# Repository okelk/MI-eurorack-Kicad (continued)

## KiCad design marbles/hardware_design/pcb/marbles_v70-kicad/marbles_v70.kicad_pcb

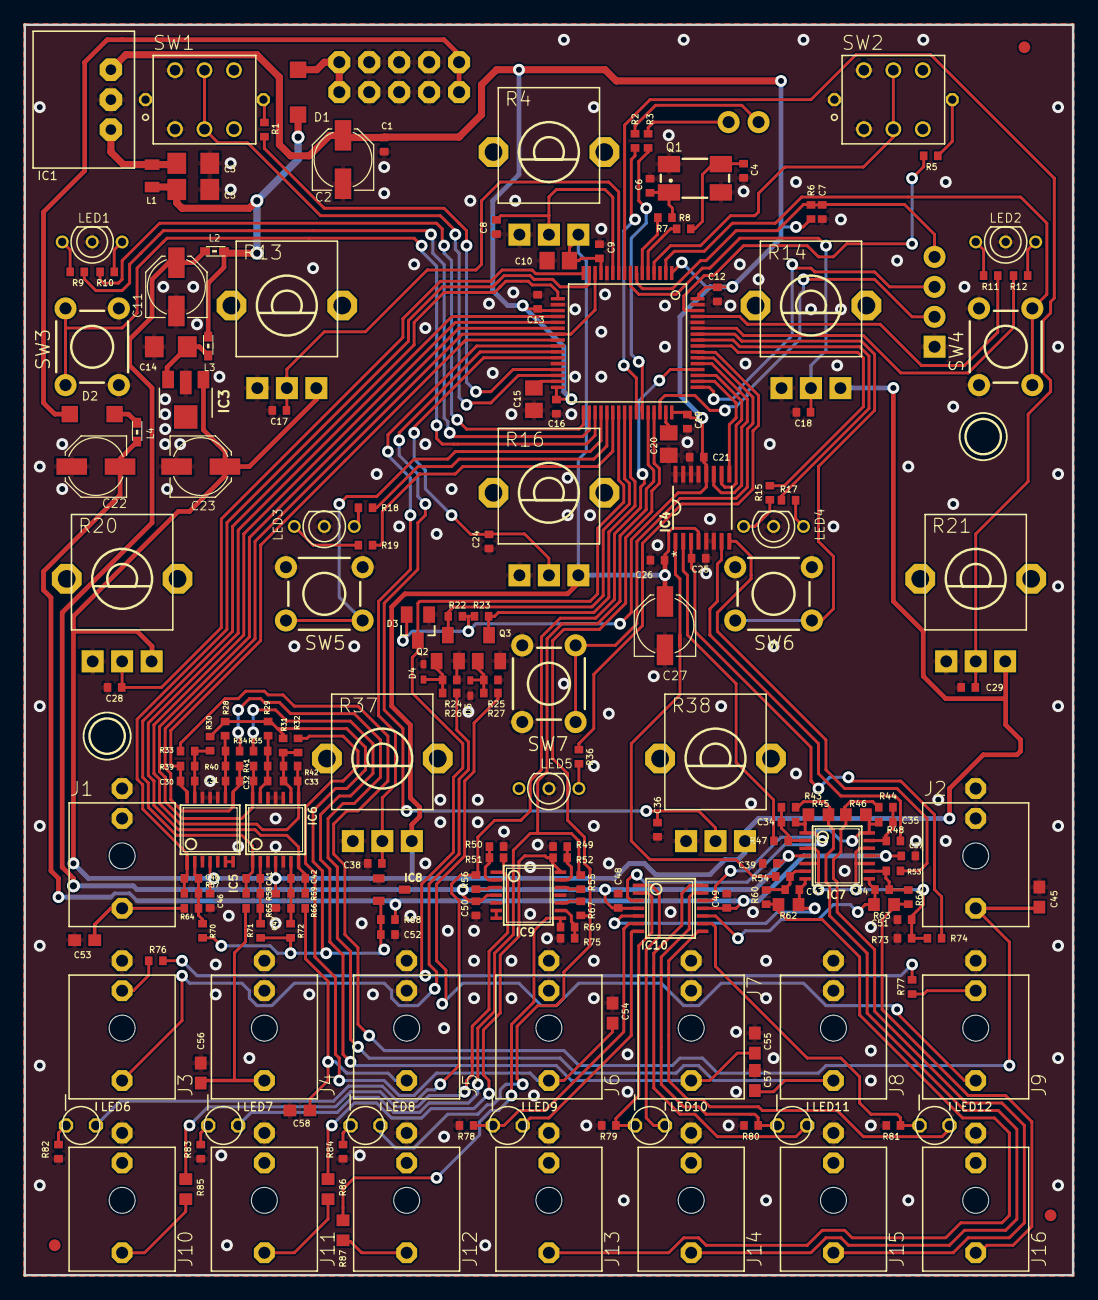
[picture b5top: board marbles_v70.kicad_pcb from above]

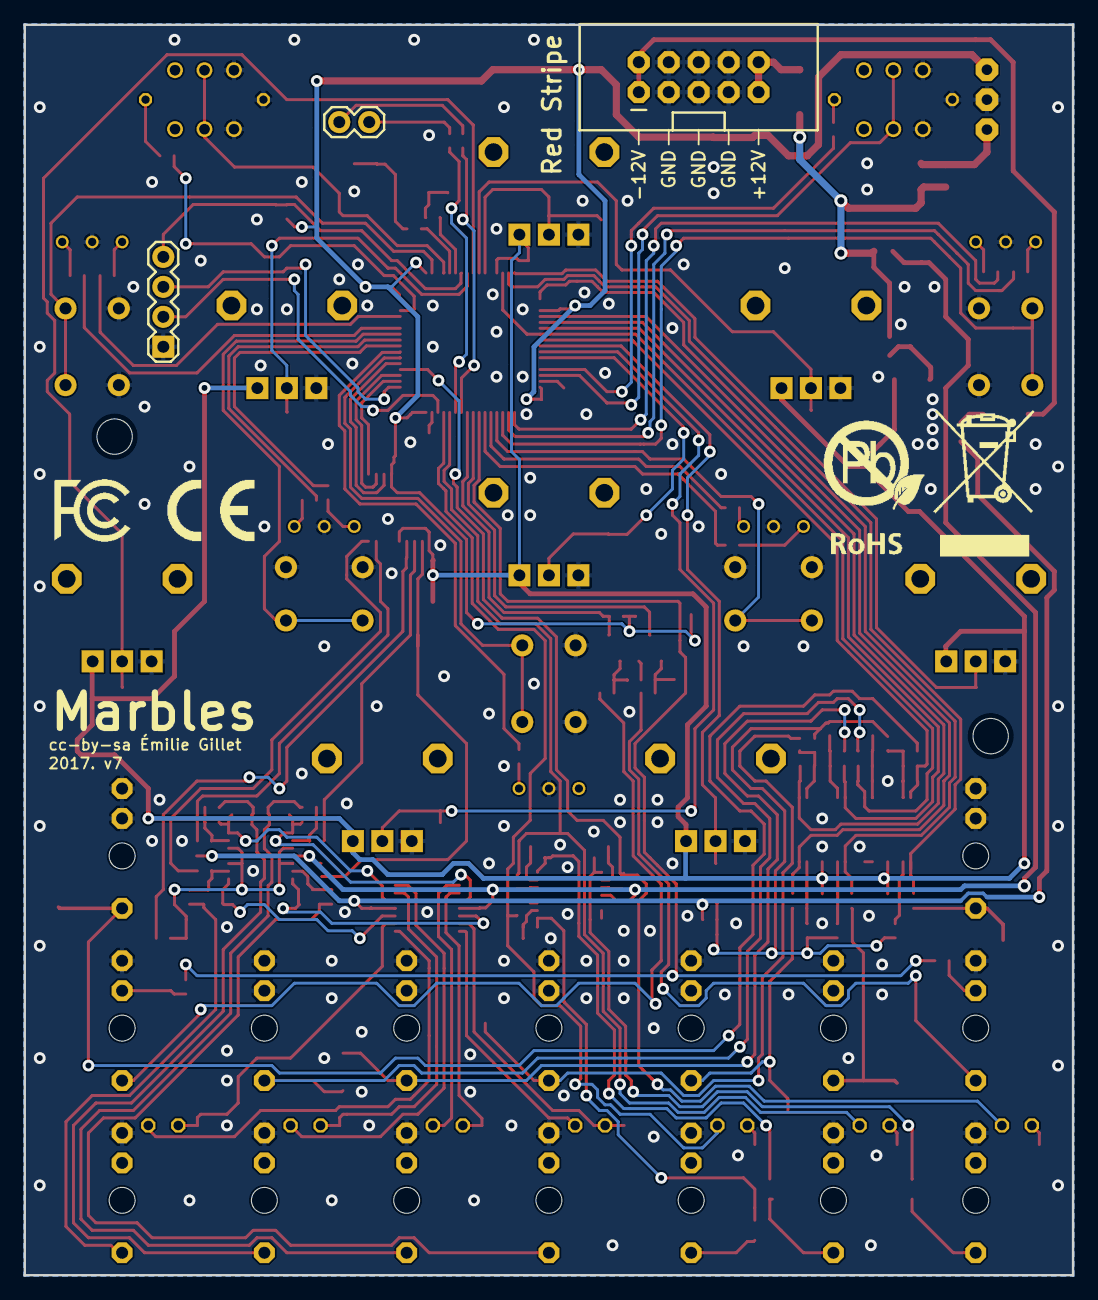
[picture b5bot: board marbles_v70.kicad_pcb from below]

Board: 2 copper layers, 88.9 x 106.0 mm, 213 parts (6 on the bottom side), 141 nets.

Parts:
C1, C7, C8, C9, C12, C13, C16, C17, C18, C19, C21, C24, C26, C28, C29, C36, C37, C38, C39, C46, C47, C48, C49, C50: 100n; C0402
C2, C11, C22, C23, C27: 22u; PANASONIC_C
C3, C5, C14: 22u; C1206
C4, C6: 20p; C0402
C10, C15, C20: 2.2u; C0805
C25, C51, C52: 470n; C0402
C30, C32, C33, C40, C42: 4.7n; C0402
C31, C41: 470p; C0402
C34, C35, C43, C44: 47p; C0402
C45, C53, C54, C55, C56, C57, C58: ESD; C0603
D1, D2: 1N5819HW; SOD123
D3: BAT54S; SOT23
D4, D5: 1N4148; SOD523
F1, F2, F3: FIDUCIAL1X2; FIDUCIAL-1X2
H3, H5: MOUNT-HOLE3.0TINY; 3,0TINY
IC1: R-78E3.3-0.5; WE78
IC2: STM32F405RGT6; TQFP-10X10-64
IC3: LD2981ABU33; SOT89
IC4: DAC8164ICPW; SOP65P640X110-16N
IC5, IC6: MCP6004; TSSOP14_065
IC7: OPA4171; TSSOP14_065
IC8: LM4040B10; DBZ_R-PDSO-G3
IC9: LM324PW; TSSOP14_065
IC10: TL074PW; TSSOP14_065
J1, J2, J3, J4, J5, J6, J7, J8, J9, J10, J11, J12, J13, J14, J15, J16: PJ301_THONKICONN6; WQP_PJ_301M6
JP1: 1X04
JP2: 1X02
JP4: M05X2SHD; 2X5-SHROUDED
L1: 33u; L2012C
L2, L3, L4: 0603
LED1, LED2, LED3, LED4, LED5: W115WSURKMGKW; LED-BICOLOR-THROUGHHOLE-2.54
LED6, LED7, LED8, LED9, LED10, LED11, LED12: WP937EGW; LED3MM
Q1: 8MHz; CTS406
Q2, Q3: MMBT3904; SOT23-BEC
R1, R5: 39; R0402
R2, R3, R7, R8: 100; R0402
R4, R13, R14, R16, R20, R21, R37, R38: 10kB; ALPS_POT_VERTICAL_PS
R6, R22, R23, R55, R56, R67: 10k; R0402
R9, R11, R15, R19: 2.2k; R0402
R10, R12, R17, R18, R36: 1.5k; R0402
R24, R25, R26, R27, R32, R33, R34, R35, R43, R44, R60, R61, R64, R65, R66, R73, R76, R77: 100k; R0402
R28, R29, R30, R31, R70, R71, R72: 200k; R0402
R39, R40, R41, R42, R57, R58, R59: 33k; R0402
R45, R46, R62, R63, R85, R86, R87: 1.0k; R0603
R47, R48, R53, R54: 23.7k; R0402
R49, R50, R75: 39k; R0402
R51, R52, R69: 56k; R0402
R68: 1.0k; R0402
R74: 150k; R0402
R78, R79, R80, R81: 680; R0402
R82, R83, R84: 180; R0402
SW1, SW2: LP4OA1PBCT
SW3, SW4, SW5, SW6, SW7: TACTILE-PTH
U$2: ROHS_BIG
U$4: CE_MEDIUM
U$5: FCC_MEDIUM

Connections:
+3V3: C1.1, C2.+, C12.1, C13.1, C16.1, C19.1, C21.1, D3.2, IC1.3, IC2.1, IC2.19, IC2.32, IC2.48, IC2.64, IC4.12, R6.2, R22.2, R23.2
+3V3_A: C9.1, C10.1, C23.+, C26.1, C27.+, C46.1, C47.1, IC2.13, IC3.1, IC4.4, IC5.4, IC6.4, R4.P$1, R13.P$1, R14.P$1, R16.P$1, R20.P$1, R21.P$1, R37.P$1, R38.P$1
ADC_DV_CV: C33.2, IC2.21, IC6.8, R42.1
ADC_DV_POT: C8.1, IC2.11, R4.P$2
ADC_LENGTH_POT: C24.1, IC2.27, R16.P$2
ADC_T_BIAS_CV: C40.2, IC2.15, IC5.1, R57.1
ADC_T_BIAS_POT: C28.1, IC2.16, R20.P$2
ADC_T_JITTER_CV: C42.2, IC2.20, IC6.7, R59.1
ADC_T_JITTER_POT: C38.1, IC2.25, R37.P$2
ADC_T_RATE_CV: C41.2, IC2.17, IC6.1, R58.1
ADC_T_RATE_POT: C17.1, IC2.10, R13.P$2
ADC_X_BIAS_CV: C30.2, IC2.24, IC5.14, R39.1
ADC_X_BIAS_POT: C29.1, IC2.9, R21.P$2
ADC_X_SPREAD_CV: C31.2, IC2.14, IC2.23, IC5.8, R40.1
ADC_X_SPREAD_POT: C18.1, IC2.8, R14.P$2
ADC_X_STEPS_CV: C32.2, IC2.22, IC6.14, R41.1
ADC_X_STEPS_POT: C36.1, IC2.26, R38.P$2
AREF_-10: C52.1, IC8.2, R28.2, R29.2, R30.2, R31.2, R68.2, R70.2, R71.2, R72.2
DAC_MOSI: IC2.53, IC4.11
DAC_SCK: IC2.51, IC4.10
DAC_SS: IC2.50, IC4.9
DAC_X_1: IC4.2, R47.2
DAC_X_2: IC4.7, R48.2
DAC_X_3: IC4.8, R53.2
DAC_Y: IC4.1, R54.2
DEPRECATED: IC5.6, IC5.7
GATE_T_1: IC2.52, LED6.1, R56.2
GATE_T_2: IC2.44, LED7.1, R55.2
GATE_T_3: IC2.45, LED8.1, R67.2
GND: C1.2, C2.-, C3.2, C4.1, C5.2, C6.1, C7.2, C8.2, C9.2, C10.2, C11.-, C12.2, C13.2, C14.2, C15.2, C16.2, C17.2, C18.2, C19.2, C20.2, C21.2, C22.+, C23.-, C24.2, C25.2, C26.2, C27.-, C28.2, C29.2, C36.2, C37.1, C38.2, C39.2, C45.2, C46.2, C47.2, C48.2, C49.1, C50.2, C51.2, C52.2, C53.2, C54.2, C55.2, C56.2, C57.2, C58.2, D3.1, D4.A, D5.A, IC1.2, IC2.12, IC2.18, IC2.28, IC2.60, IC2.63, IC3.2, IC4.5, IC4.6, IC4.13, IC4.14, IC4.15, IC4.16, IC5.3, IC5.5, IC5.10, IC5.11, IC5.12, IC6.3, IC6.5, IC6.10, IC6.11, IC6.12, IC8.1, IC9.5, IC9.11, J1.P1, J1.P2, J2.P1, J2.P2, J3.P1, J4.P1, J4.P2, J5.P1, J5.P2, J6.P1, J6.P2, J7.P1, J7.P2, J8.P1, J8.P2, J9.P1, J10.P1, J11.P1, J12.P1, J13.P1, J14.P1, J15.P1, J16.P1, JP1.1, JP4.3, JP4.4, JP4.5, JP4.6, JP4.7, JP4.8, LED1.2, LED2.2, LED3.2, LED4.2, LED5.2, Q1.2, Q1.4, Q2.E, Q3.E, R4.P$3, R13.P$3, R14.P$3, R16.P$3, R20.P$3, R21.P$3, R24.1, R25.1, R37.P$3, R38.P$3, R49.2, R50.2, R73.1, R75.2, R78.2, R79.2, R80.2, R81.2, R82.1, R83.1, R84.1, SW1.L2, SW1.P3, SW1.P6, SW2.L2, SW2.P3, SW2.P6, SW3.1, SW3.2, SW4.1, SW4.2, SW5.1, SW5.2, SW6.1, SW6.2, SW7.1, SW7.2
LED_T_DV: IC2.29, R1.1
LED_T_MODE_G: IC2.33, R10.1
LED_T_MODE_R: IC2.34, R9.1
LED_T_RANGE_G: IC2.37, R18.1
LED_T_RANGE_R: IC2.38, R19.1
LED_X_DV: IC2.62, R5.1
LED_X_EXT_G: IC2.55, R36.1
LED_X_MODE_G: IC2.59, R12.1
LED_X_MODE_R: IC2.61, R11.1
LED_X_RANGE_G: IC2.57, R17.1
LED_X_RANGE_R: IC2.56, R15.1
MORPH_IN: C53.1, J1.P3, R64.2
MORPH_IN1: C55.1, J7.P3, R35.2
MORPH_IN3: C56.1, J4.P3, R65.2
MORPH_IN4: C57.1, J8.P3, R34.2
MORPH_IN5: C54.1, J6.P3, R32.2
MORPH_IN6: C58.1, J5.P3, R66.2
MORPH_IN7: C45.1, J2.P3, R33.2
unnamed: R1.2, SW1.L1
unnamed: R5.2, SW2.L1
unnamed: IC9.12, R55.1
unnamed: C14.1, IC3.3, L3.1
unnamed: C41.1, IC6.2, R58.2, R65.1, R71.1
unnamed: C5.1, D1.C, L1.1, L2.2, L3.2
unnamed: IC2.6, R7.1
unnamed: IC2.5, R8.1
unnamed: LED3.3, R19.2
unnamed: D2.A, L4.2
unnamed: C40.1, IC5.2, R57.2, R64.1, R70.1
unnamed: LED3.1, R18.2
unnamed: C20.1, IC2.47
unnamed: IC9.1, R51.1, R85.2
unnamed: C42.1, IC6.6, R59.2, R66.1, R72.1
unnamed: LED1.3, R9.2
unnamed: C31.1, IC5.9, R28.1, R34.1, R40.2
unnamed: LED2.3, R11.2
unnamed: C15.1, IC2.31
unnamed: LED2.1, R12.2
unnamed: LED4.3, R15.2
unnamed: LED1.1, R10.2
unnamed: LED4.1, R17.2
unnamed: J10.P3, R85.1
unnamed: C30.1, IC5.13, R30.1, R33.1, R39.2
unnamed: IC9.2, R50.1, R51.2
unnamed: C32.1, IC6.13, R29.1, R35.1, R41.2
unnamed: LED6.2, R82.2
unnamed: IC9.3, R56.1
unnamed: IC9.6, IC9.7
unnamed: C33.1, IC6.9, R31.1, R32.1, R42.2
unnamed: C3.1, IC1.1, L1.2
unnamed: JP2.2, R2.1
unnamed: IC9.14, R52.1, R86.2
unnamed: IC9.13, R49.1, R52.2
unnamed: J9.P3, R27.1
unnamed: IC9.10, R67.1
unnamed: IC9.8, R69.1, R87.2
unnamed: J11.P3, R86.1
unnamed: J12.P3, R87.1
unnamed: IC9.9, R69.2, R75.1
unnamed: LED5.1, R36.2
unnamed: LED7.2, R83.2
unnamed: C43.2, IC7.7, IC10.5, R62.2
unnamed: J9.P2, R77.2
unnamed: J3.P2, R76.2
unnamed: LED8.2, R84.2
unnamed: J15.P3, R44.1, R46.1
unnamed: D4.C, Q2.B, R24.2, R26.2
unnamed: JP2.1, R3.1
unnamed: D5.C, Q3.B, R25.2, R27.2
unnamed: J13.P3, R60.1, R62.1
unnamed: C35.1, IC7.13, R44.2, R48.1
unnamed: D1.A, JP4.9, JP4.10
unnamed: J3.P3, R26.1
unnamed: J16.P3, R61.1, R63.1
unnamed: C44.1, IC7.9, R53.1, R61.2
unnamed: C34.1, IC7.2, R43.2, R47.1
unnamed: C43.1, IC7.6, R54.1, R60.2
unnamed: C4.2, Q1.3, R8.2
unnamed: J14.P3, R43.1, R45.1
unnamed: D2.C, JP4.1, JP4.2
unnamed: C6.2, Q1.1, R7.2
unnamed: IC10.6, LED9.2, R78.1
unnamed: IC10.7, LED9.1
unnamed: C34.2, IC7.1, IC10.3, R45.2
unnamed: IC10.2, LED10.2, R79.1
unnamed: IC10.1, LED10.1
unnamed: C35.2, IC7.14, IC10.12, R46.2
unnamed: IC10.13, LED11.2, R80.1
unnamed: IC10.14, LED11.1
unnamed: C44.2, IC7.8, IC10.10, R63.2
unnamed: IC10.9, LED12.2, R81.1
unnamed: IC10.8, LED12.1
NORMALIZATION_PROBE: D3.3, IC2.39, R76.1, R77.1
RESET: C7.1, IC2.7, JP1.4, R6.1
RX: IC2.43, R3.2
SWCLK: IC2.49, JP1.3
SWDIO: IC2.46, JP1.2
SW_T_DV: IC2.30, SW1.P2, SW1.P5
SW_T_MODE: IC2.35, SW3.3, SW3.4
SW_T_RANGE: IC2.36, SW5.3, SW5.4
SW_X_DV: IC2.4, SW2.P2, SW2.P5
SW_X_EXT: IC2.54, SW7.3, SW7.4
SW_X_MODE: IC2.2, SW4.3, SW4.4
SW_X_RANGE: IC2.58, SW6.3, SW6.4
TX: IC2.42, R2.2
T_CLOCK: IC2.40, Q2.C, R22.1
VCC: C11.+, C39.1, C48.1, C50.1, IC7.4, IC9.4, IC10.4, L2.1
VEE: C22.-, C37.2, C49.2, IC7.11, IC10.11, L4.1, R68.1
VREF: C25.1, IC4.3, R74.2
VREF_BIAS: C51.1, IC7.3, IC7.5, IC7.10, IC7.12, R73.2, R74.1
X_CLOCK: IC2.41, Q3.C, R23.1

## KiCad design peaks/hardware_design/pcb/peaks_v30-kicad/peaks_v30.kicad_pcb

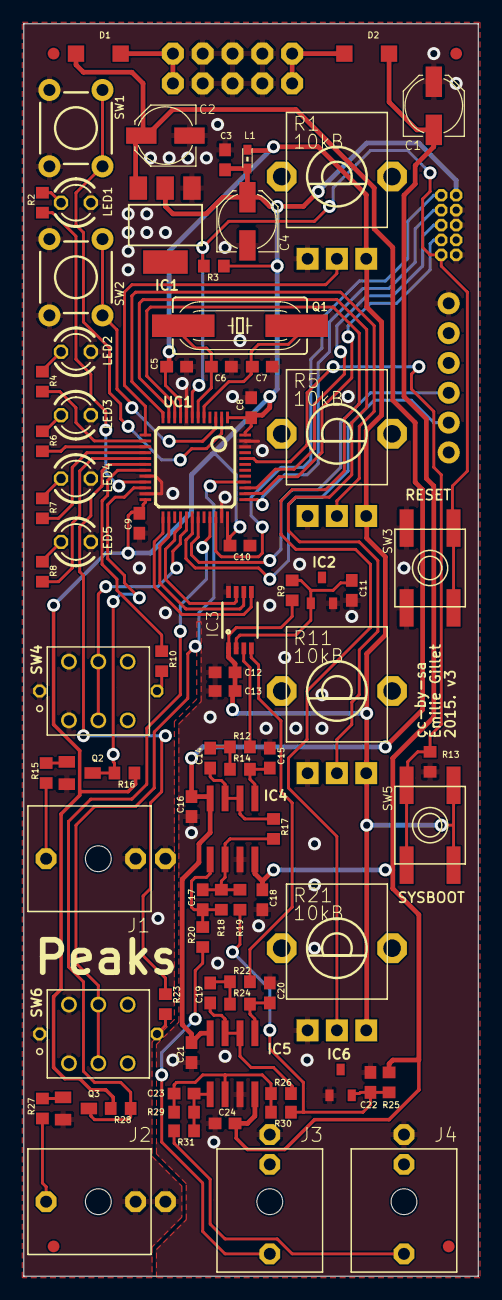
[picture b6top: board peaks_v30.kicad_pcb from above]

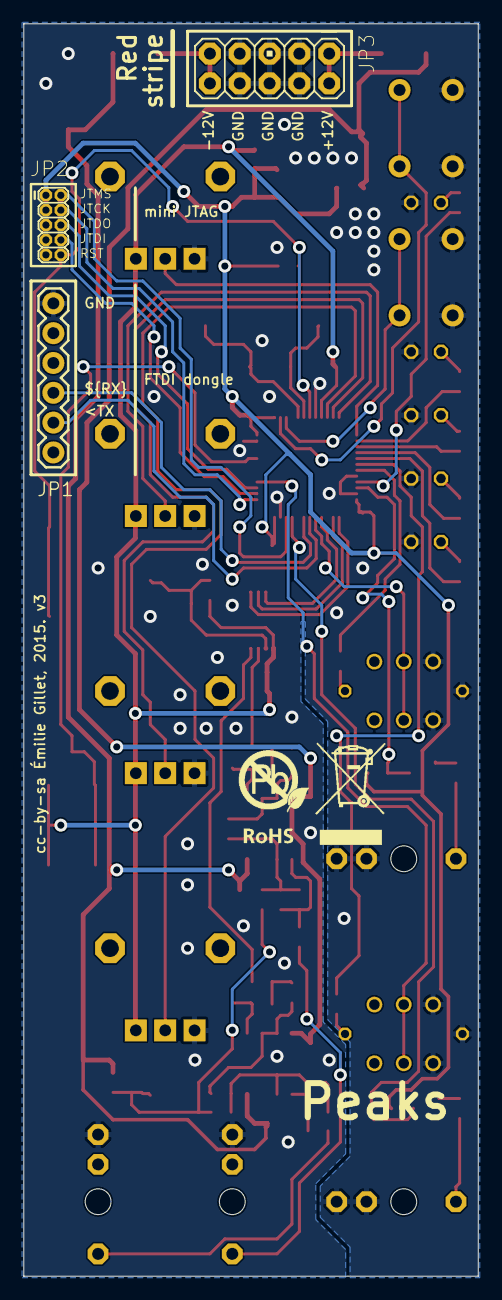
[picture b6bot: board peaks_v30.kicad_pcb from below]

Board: 2 copper layers, 38.7 x 106.7 mm, 91 parts (4 on the bottom side), 64 nets.

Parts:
C1, C2, C4: 22u; PANASONIC_C
C3, C5, C8, C9, C10, C12, C16, C18, C21, C24: 100n; C0603
C6, C7, C17, C23: 18p; C0603
C11, C22: 470n; C0603
C13: 3.3u; C0603
C14, C15, C19, C20: 220p; C0603
D1, D2: 1N5819HW; SOD123
F1, F2, F3, F4: FIDUCIAL1X2; FIDUCIAL-1X2
IC1: LM1117-3.3; SOT223
IC2: LM4040B25; DBZ_R-PDSO-G3
IC3: DAC8552; MSOP-8
IC4, IC5: OPA2171; SO08
IC6: LM4040B10; DBZ_R-PDSO-G3
J1, J2, J3, J4: PJ301_THONKICONN6; WQP_PJ_301M6
JP1: 1X06
JP2: M05X2MINIJTAG; 2X5-1.27
JP3: M05X2PTH; AVR_ICSP
L1: 0603
LED1, LED2, LED3, LED4, LED5: LED3MM
Q1: 8MHz; HC49UP
Q2, Q3: MMBT3904; SOT23-BEC
R1, R5, R11, R21: 10kB; ALPS_POT_VERTICAL_PS
R2, R4, R6, R7, R8: 100; R0603
R3, R13, R16, R28: 10k; R0603
R9, R25: 3.3k; R0603
R10, R23: 33; R0603
R12, R14, R17, R22, R24, R26: 39k; R0603
R15, R27: 100k; R0603
R18, R29: 249k; R0603
R19, R30: 309k; R0603
R20, R31: 1.0k; R0603
SW1, SW2: TACTILE-PTH
SW3, SW5: EVQ-Q2
SW4, SW6: LP4OA1PBCT
U$2: ROHS
UC1: STM32F103CBT6; LQFP48

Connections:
+3V3: C3.1, C4.+, C8.1, C9.1, C10.1, IC1.2, JP2.1, L1.1, R3.2, R16.2, R28.2, UC1.1, UC1.24, UC1.36, UC1.48
+3V3_A: C5.1, C12.1, C13.1, IC3.1, L1.2, R1.P$1, R5.P$1, R9.1, R11.P$1, R21.P$1, SW5.B, SW5.B', UC1.9
A: IC3.4, R22.2
AREF_2.5: C11.1, IC2.1, IC3.2, R9.2
AREF_-10: C22.1, IC6.2, R19.2, R25.2, R30.2
B: IC3.3, R12.2
BI_OUT: C17.2, IC4.1, R18.1, R20.2
BI_OUT1: C23.2, IC5.1, R29.1, R31.2
BOOT_FLASH: R13.2, SW5.A, SW5.A', UC1.44
DAC_MOSI: IC3.7, UC1.28
DAC_SCK: IC3.6, UC1.26
DAC_SS: IC3.5, UC1.25
F_CV: C17.1, IC4.2, R17.1, R18.2, R19.1
F_CV1: C23.1, IC5.2, R26.1, R29.2, R30.1
GND: C1.+, C2.-, C3.2, C4.-, C5.2, C6.1, C7.1, C8.2, C9.2, C10.2, C11.2, C12.2, C13.2, C15.2, C16.2, C18.1, C20.2, C21.2, C22.2, C24.1, IC1.1, IC2.2, IC3.8, IC4.3, IC5.3, IC6.1, J1.P1, J1.P2, J2.P1, J2.P2, J3.P1, J4.P1, JP1.1, JP2.3, JP2.5, JP2.9, JP3.3, JP3.4, JP3.5, JP3.6, JP3.7, JP3.8, LED1.K, LED2.K, LED3.K, LED4.K, LED5.K, Q2.E, Q3.E, R1.P$3, R5.P$3, R11.P$3, R13.1, R21.P$3, SW1.1, SW1.2, SW2.1, SW2.2, SW3.A, SW3.A', SW4.L2, SW4.P3, SW4.P6, SW6.L2, SW6.P3, SW6.P6, UC1.8, UC1.20, UC1.23, UC1.35, UC1.46, UC1.47
JTCK: JP2.4, UC1.37
JTDI: JP2.8, UC1.38
JTDO: JP2.6, UC1.39
JTMS: JP2.2, UC1.34
unnamed: J1.P3, R15.1
unnamed: R23.2, UC1.18
unnamed: LED2.A, R4.1
unnamed: LED3.A, R6.1
unnamed: LED4.A, R7.1
unnamed: LED5.A, R8.1
unnamed: C7.2, Q1.2, UC1.5
unnamed: C6.2, Q1.1, UC1.6
unnamed: R10.2, UC1.19
unnamed: R4.2, UC1.14
unnamed: R6.2, UC1.15
unnamed: R7.2, UC1.16
unnamed: R8.2, UC1.17
unnamed: Q2.B, R15.2
unnamed: C19.2, IC5.6, IC5.7, R26.2
unnamed: R23.1, SW6.L1
unnamed: R10.1, SW4.L1
unnamed: LED1.A, R2.1
unnamed: R2.2, UC1.21
unnamed: C20.1, IC5.5, R24.1
unnamed: C19.1, R22.1, R24.2
unnamed: J3.P3, R20.1
unnamed: J4.P3, R31.1
unnamed: C14.2, IC4.6, IC4.7, R17.2
unnamed: C15.1, IC4.5, R14.1
unnamed: C14.1, R12.1, R14.2
unnamed: D1.A, JP3.1, JP3.2
unnamed: J2.P3, R27.1
unnamed: D2.C, JP3.9, JP3.10
unnamed: Q3.B, R27.2
POT_1: R1.P$2, UC1.13
POT_2: R5.P$2, UC1.12
POT_3: R11.P$2, UC1.11
POT_4: R21.P$2, UC1.10
RESET: JP2.10, R3.1, SW3.B, SW3.B', UC1.7
RX: JP1.4, UC1.31
SW_DUAL: SW2.3, SW2.4, UC1.3
SW_MODE: SW1.3, SW1.4, UC1.2
SW_TRIG_1: SW6.P2, SW6.P5, UC1.40
SW_TRIG_2: SW4.P2, SW4.P5, UC1.29
TRIG_1: Q3.C, R28.1, UC1.33
TRIG_2: Q2.C, R16.1, UC1.22
TX: JP1.5, UC1.30
VCC: C2.+, C16.1, C21.1, D1.C, IC1.3, IC4.8, IC5.8
VEE: C1.-, C18.2, C24.2, D2.A, IC4.4, IC5.4, R25.1

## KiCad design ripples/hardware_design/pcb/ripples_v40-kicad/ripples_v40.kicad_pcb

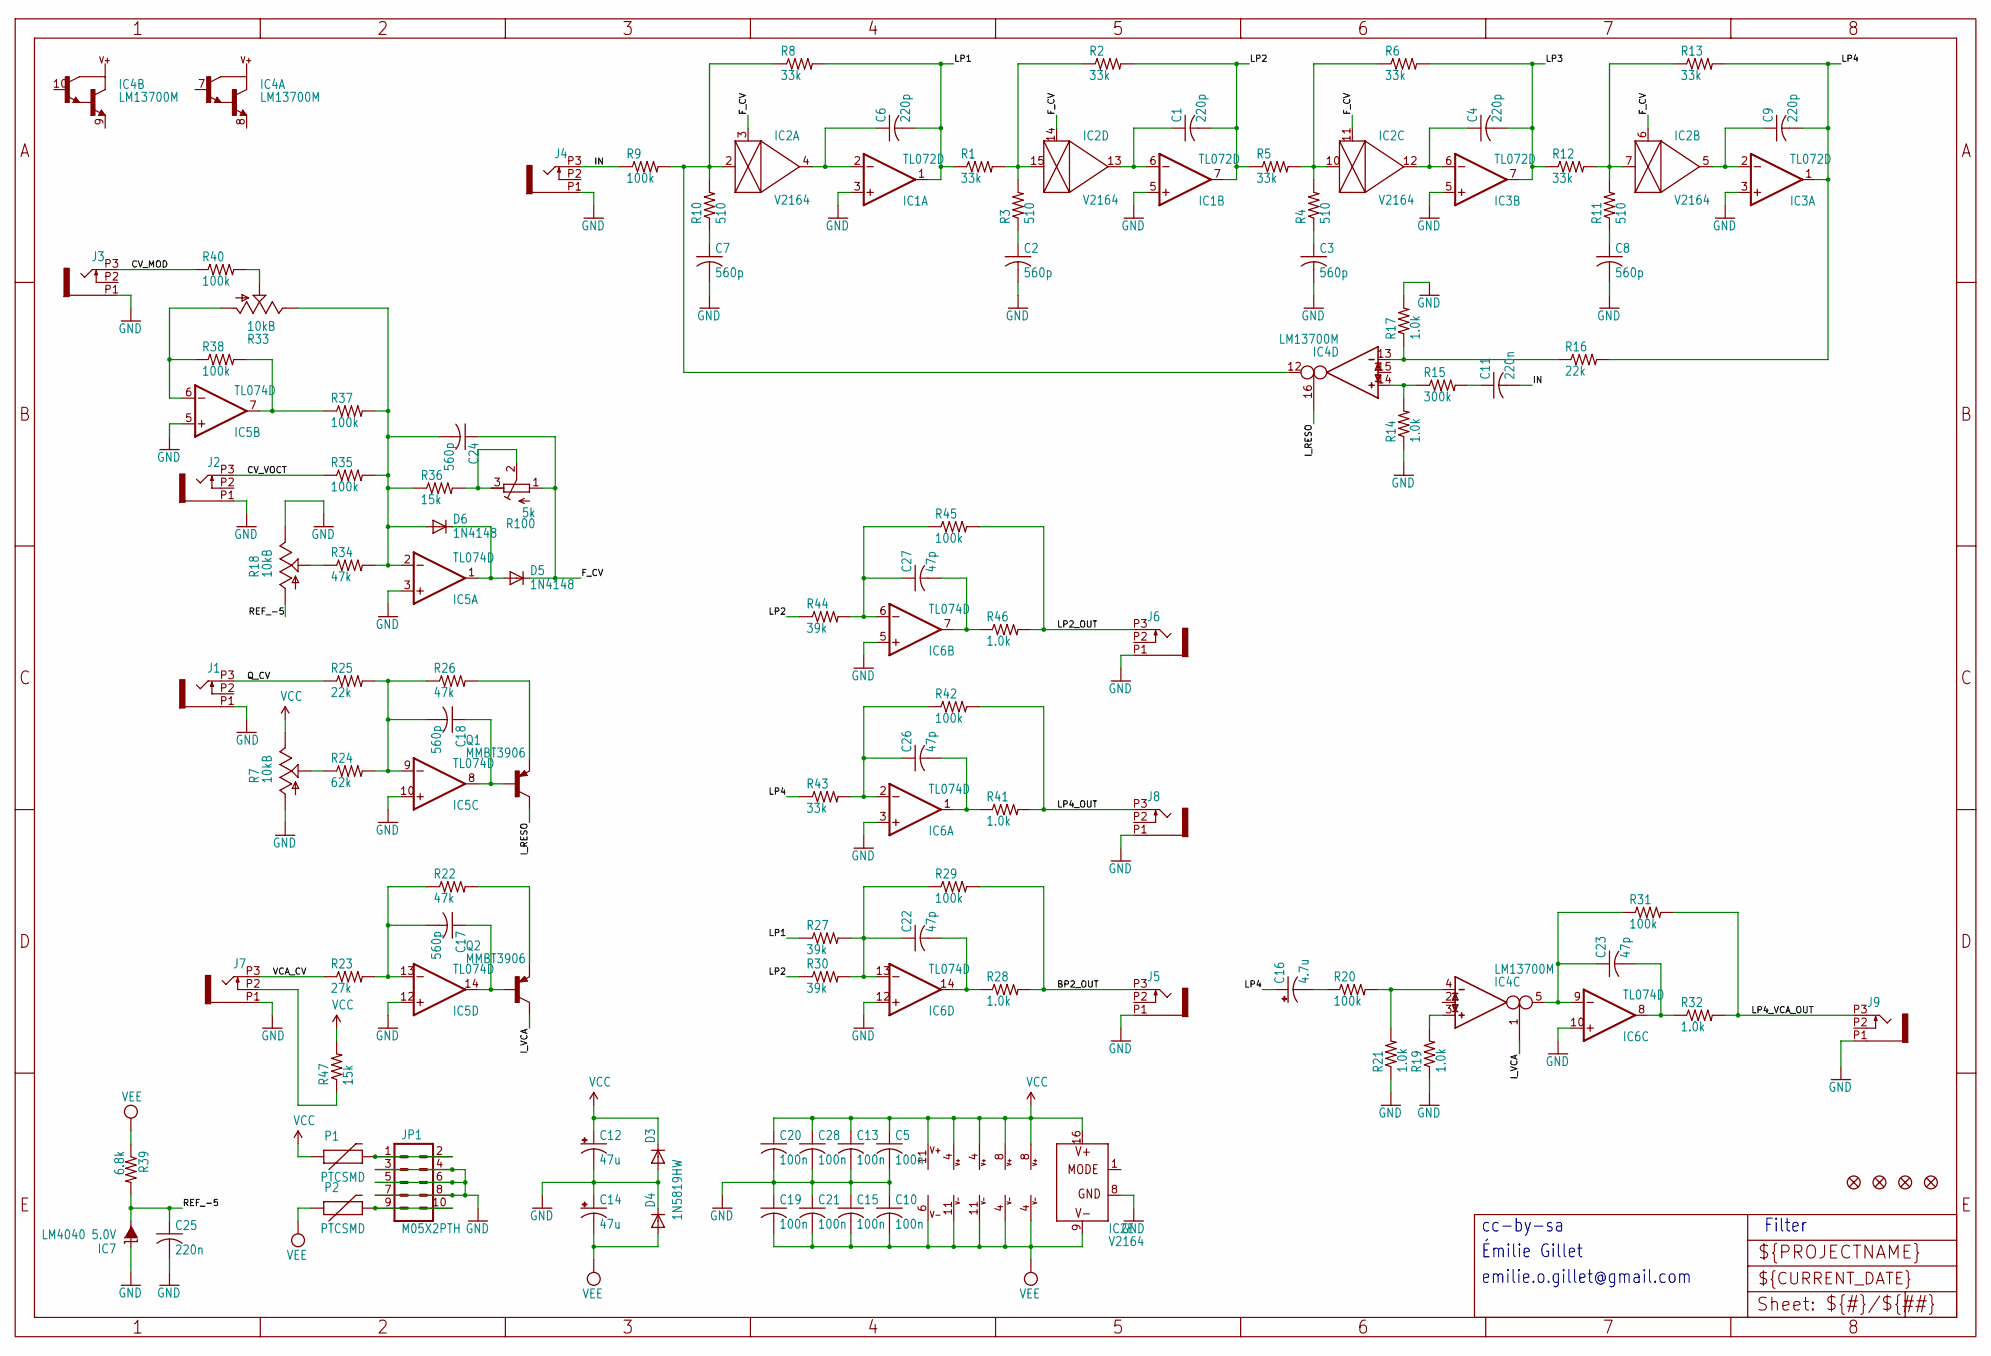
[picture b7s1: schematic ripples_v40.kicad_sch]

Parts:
C1, C4, C6, C9: 220p; C0603
C2, C3, C7, C8, C17, C18, C24: 560p; C0603
C5, C10, C13, C15, C19, C20, C21, C28: 100n; C0603
C11, C25: 220n; C0603
C12, C14: 47u; PANASONIC_D
C16: 4.7u; PANASONIC_B
C22, C23, C26, C27: 47p; C0603
D3, D4: 1N5819HW; SOD123
D5, D6: 1N4148; SOD323-W
F1, F2, F3, F4: FIDUCIAL1X2; FIDUCIAL-1X2
IC1, IC3: TL072D; SO08
IC2: V2164; SOIC16N
IC4: LM13700M; SO16
IC5, IC6: TL074D; SO14
IC7: LM4040 5.0V; DBZ_R-PDSO-G3
J1, J2, J3, J4, J5, J6, J7, J8, J9: PJ301_THONKICONN6; WQP_PJ_301M6
JP1: M05X2PTH; AVR_ICSP
P1, P2: PTCSMD; PTC-1206
Q1, Q2: MMBT3906; SOT23-BEC
R1, R2, R5, R6, R8, R12, R13, R43: 33k; R0603
R3, R4, R10, R11: 510; R0603
R7, R18, R33: 10kB; ALPS_POT_VERTICAL_PS
R9, R20, R29, R31, R35, R37, R38, R40, R42, R45: 100k; R0603
R14, R17, R19, R21, R28, R32, R41, R46: 1.0k; R0603
R15: 300k; R0603
R16, R25: 22k; R0603
R22, R26, R34: 47k; R0603
R23: 27k; R0603
R24: 62k; R0603
R27, R30, R44: 39k; R0603
R36, R47: 15k; R0603
R39: 6.8k; R0603
R100: 5k; RTRIM3296X

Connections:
BP2_OUT: J5.P3 (3), R28.2, R29.2
CV_F_POT: R18.P$2 (S), R34.1
CV_MOD: J3.P3 (3), R40.1
CV_VOCT: J2.P3 (3), R35.1
F_CV: C24.1, D5.C, IC2.3 (CTRL), IC2.6 (CTRL), IC2.11 (CTRL), IC2.14 (CTRL), R100.1 (E)
GND: C2.2, C3.2, C5.2, C7.2, C8.2, C10.1, C12.-, C13.2, C14.+, C15.1, C19.1, C20.2, C21.1, C25.2, C28.2, D3.A, D4.C, IC1.3 (+IN), IC1.5 (+IN), IC2.8 (GND), IC3.3 (+IN), IC3.5 (+IN), IC5.3 (+IN), IC5.5 (+IN), IC5.10 (+IN), IC5.12 (+IN), IC6.3 (+IN), IC6.5 (+IN), IC6.10 (+IN), IC6.12 (+IN), IC7.1 (C), J1.P1 (1), J2.P1 (1), J3.P1 (1), J4.P1 (1), J5.P1 (1), J6.P1 (1), J7.P1 (1), J8.P1 (1), J9.P1 (1), JP1.3, JP1.4, JP1.5, JP1.6, JP1.7, JP1.8, R7.P$3 (A), R14.1, R17.2, R18.P$1 (E), R19.1, R21.1
IN: C11.2, J4.P3 (3), R9.1
I_RESO: IC4.16 (I_BIAS), Q1.C
I_VCA: IC4.1 (I_BIAS), Q2.C
LP1: C6.2, IC1.1 (OUT), R1.1, R8.2, R27.1
LP2: C1.2, IC1.7 (OUT), R2.2, R5.1, R30.1, R44.1
LP2_OUT: J6.P3 (3), R45.2, R46.2
LP3: C4.2, IC3.7 (OUT), R6.2, R12.1
LP4: C9.2, C16.+, IC3.1 (OUT), R13.2, R16.2, R43.1
LP4_OUT: J8.P3 (3), R41.2, R42.2
LP4_VCA_OUT: J9.P3 (3), R31.2, R32.2
unnamed: IC5.7 (OUT), R37.1, R38.2
unnamed: C6.1, IC1.2 (-IN), IC2.4 (OUT)
unnamed: IC2.15 (IN), R1.2, R2.1, R3.2
unnamed: R36.2, R100.2 (S), R100.3 (A)
unnamed: IC4.3 (IN_P), R19.2
unnamed: JP1.1, JP1.2, P1.2
unnamed: C11.1, R15.2
unnamed: C7.1, R10.1
unnamed: C1.1, IC1.6 (-IN), IC2.13 (OUT)
unnamed: IC2.2 (IN), IC4.12 (OUT), R8.1, R9.2, R10.2
unnamed: C2.1, R3.1
unnamed: IC2.10 (IN), R4.2, R5.2, R6.1
unnamed: C4.1, IC2.12 (OUT), IC3.6 (-IN)
unnamed: IC4.13 (IN_N), R16.1, R17.1
unnamed: C3.1, R4.1
unnamed: IC2.7 (IN), R11.2, R12.2, R13.1
unnamed: C9.1, IC2.5 (OUT), IC3.2 (-IN)
unnamed: IC4.14 (IN_P), R14.2, R15.1
unnamed: C8.1, R11.1
unnamed: JP1.9, JP1.10, P2.2
unnamed: R33.P$2 (S), R40.2
unnamed: IC5.6 (-IN), R33.P$3 (A), R38.1
unnamed: C24.2, D6.A, IC5.2 (-IN), R33.P$1 (E), R34.2, R35.2, R36.1, R37.2
unnamed: R7.P$2 (S), R24.1
unnamed: C17.2, IC5.13 (-IN), R22.1, R23.2
unnamed: C18.2, IC5.9 (-IN), R24.2, R25.2, R26.1
unnamed: C18.1, IC5.8 (OUT), Q1.B
unnamed: Q1.E, R26.2
unnamed: J7.P2 (2), R47.1
unnamed: C17.1, IC5.14 (OUT), Q2.B
unnamed: Q2.E, R22.2
unnamed: C27.1, IC6.6 (-IN), R44.2, R45.1
unnamed: C26.1, IC6.2 (-IN), R42.1, R43.2
unnamed: C26.2, IC6.1 (OUT), R41.1
unnamed: D5.A, D6.C, IC5.1 (OUT)
unnamed: C27.2, IC6.7 (OUT), R46.1
unnamed: C22.1, IC6.13 (-IN), R27.2, R29.1, R30.2
unnamed: C22.2, IC6.14 (OUT), R28.1
unnamed: IC4.4 (IN_N), R20.2, R21.2
unnamed: C23.1, IC4.5 (OUT), IC6.9 (-IN), R31.1
unnamed: C23.2, IC6.8 (OUT), R32.1
unnamed: C16.-, R20.1
Q_CV: J1.P3 (3), R25.1
REF_-5: C25.1, IC7.2 (A), R18.P$3 (A), R39.2
VCA_CV: J7.P3 (3), R23.1
VCC: C5.1, C12.+, C13.1, C20.1, C28.1, D3.C, IC1.8 (V+), IC2.16 (V+), IC3.8 (V+), IC4.11 (V+), IC5.4 (V+), IC6.4 (V+), P1.1, R7.P$1 (E), R47.2
VEE: C10.2, C14.-, C15.2, C19.2, C21.2, D4.A, IC1.4 (V-), IC2.9 (V-), IC3.4 (V-), IC4.6 (V-), IC5.11 (V-), IC6.11 (V-), P2.1, R39.1

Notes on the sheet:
Émilie Gillet
emilie.o.gillet@gmail.com
cc-by-sa
Filter

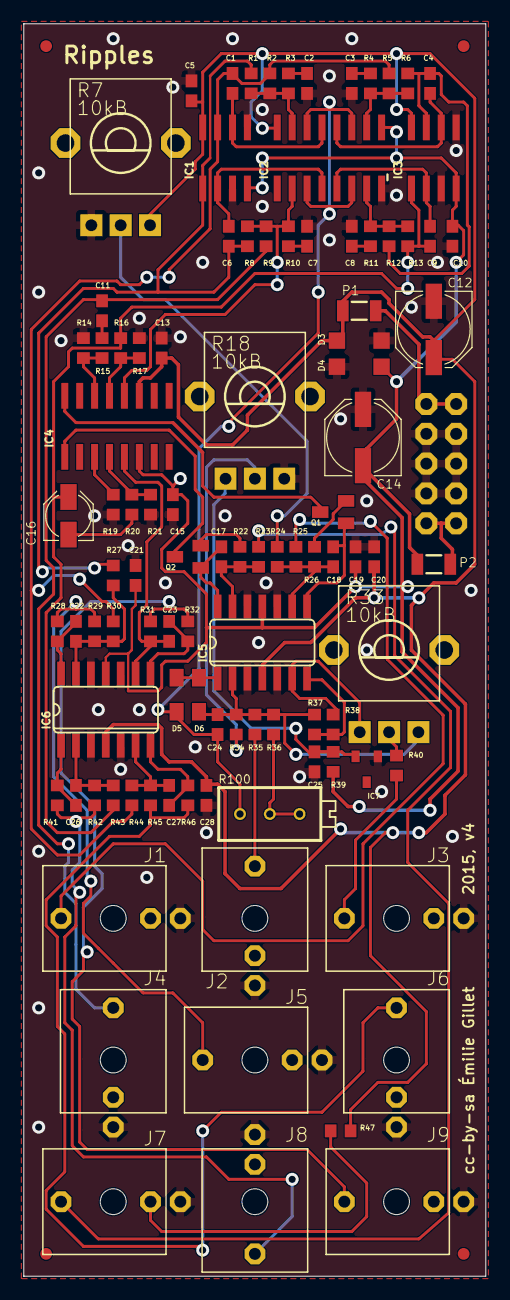
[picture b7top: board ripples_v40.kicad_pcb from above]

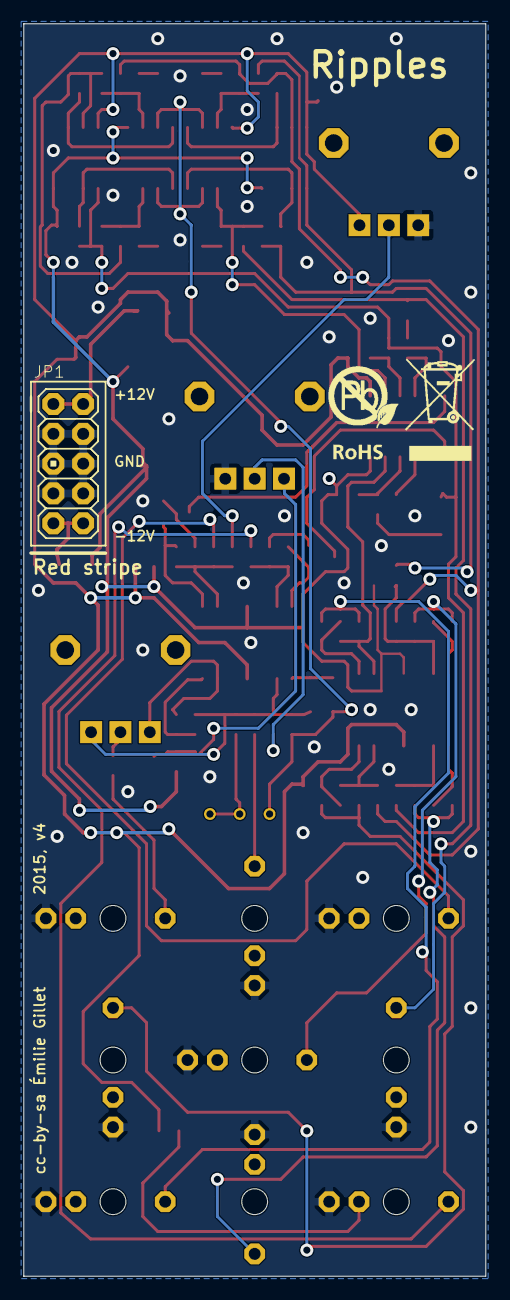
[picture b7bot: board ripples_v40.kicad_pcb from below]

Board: 2 copper layers, 39.3 x 106.7 mm, 106 parts (2 on the bottom side), 63 nets.

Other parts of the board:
U$2: ROHS
